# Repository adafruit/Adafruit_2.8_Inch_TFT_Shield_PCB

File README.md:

# 2.8" TFT Touch Shield for Arduino 

We've discontinued this version of the shield (which was expensive and difficult to make) and [replaced it with a version 2: its got a better price, uses way fewer pins, is Mega/Leonardo compatible and has a great touchscreen controller built in. Wow! Check it out here.](http://www.adafruit.com/products/1651)

Spice up your Arduino project with a beautiful large touchscreen display shield with built in microSD card connection. This TFT display is big (2.8" diagonal) bright (4 white-LED backlight) and colorful (18-bit 262,000 different shades)! 240x320 pixels with individual pixel control. It has way more resolution than a black and white 128x64 display. As a bonus, this display has a resistive touchscreen attached to it already, so you can detect finger presses anywhere on the screen.

__The shield is fully assembled, tested and ready to go. No wiring, no soldering! Simply plug it in and load up our library - you'll have it running in under 10 minutes!__ Works best with any classic Arduino (UNO/Duemilanove/Diecimila). This shield does work with the Mega Arduinos __but its going to be half the speed of the Uno-type boards__ because of the way the Mega rearranges all the pins (there is no way to get around this!) This shield is not Leonardo-compatible

This display shield has a controller built into it with RAM buffering, so that almost no work is done by the microcontroller. The shield does require a lot of pins: 12 lines total for the display, 13 total if you use the microSD card

[Of course, we wouldn't just leave you with a datasheet and a "good luck!" - we've written a full open source graphics library that can draw pixels, lines, rectangles, circles and text. We also have a touch screen library that detects x, y and z (pressure) and example code to demonstrate all of it. The code is written for Arduino but can be easily ported to your favorite microcontroller!](http://learn.adafruit.com/2-8-tft-touch-shield).

If you are not using an Arduino-shaped microcontroller, [check out our 2.8" TFT breakout board which can be easily wired up to any processor](http://www.adafruit.com/products/335) the breakout board version does not have microSD holder.

### TECHNICAL DETAILS

- 2.8" diagonal LCD TFT display
- 240x320 resolution, 18-bit (262,000) color
- ILI9325 (datasheet) or ILI9328 (datasheet) or HX8347 (datasheet) controller with built in video RAM buffer
- 8 bit digital interface, plus 4 control lines
- Uses digital pins 5-13 and analog 0-3. That means you can use digital pins 2, 3 and analog 4 and 5. Pin 12 is available if not using the microSD
- Works with any Arduino '328 or Mega (Leonardo not supported yet)
- 5V compatible! Use with 3.3V or 5V logic
- Onboard 3.3V @ 300mA LDO regulator
- 4 white LED backlight. On by default but you can connect the transistor to a digital pin for backlight control
- 4-wire resistive touchscreen

### License

Adafruit invests time and resources providing this open source design, please support Adafruit and open-source hardware by purchasing products from [Adafruit](https://www.adafruit.com)!

Designed by Limor Fried/Ladyada for Adafruit Industries.

Creative Commons Attribution/Share-Alike, all text above must be included in any redistribution. See license.txt for additional details.

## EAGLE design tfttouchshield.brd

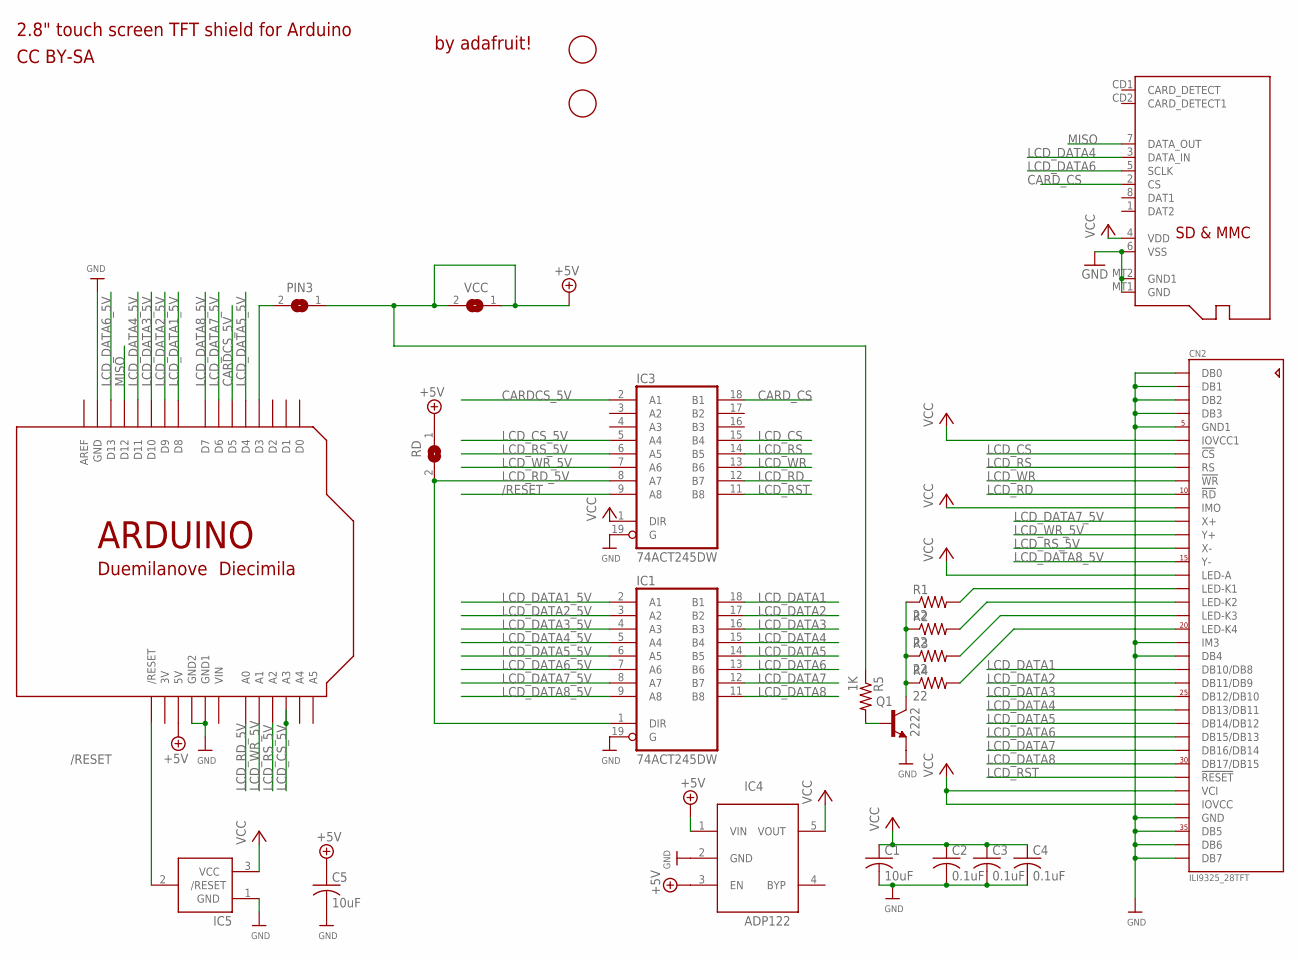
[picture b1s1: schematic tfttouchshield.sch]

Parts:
C1, C5: 10uF; C0805K
C2, C3, C4: 0.1uF; C0805K
CN2: ILI9325_28TFT; ILI9325_28INCH_TS
IC1, IC3: 74ACT245DW; SO20W
IC4: ADP122; SOT23-5L
IC5: AXP083-SAG; SOT23
PIN3: SJ
Q1: 2222; SOT23-BEC
R1, R2, R3, R4: 22; R0805
R5: 1K; R0805
RD: SJ
U$2: ARDUINO-NOHOLE
U$3: MICROSD
U$10, U$11: FIDUCIAL; FIDUCIAL_1MM
VCC: SJ

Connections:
3V: U$2.3V
+5V: C5.1, IC4.1 (VIN), IC4.3 (EN), PIN3.1, R5.1, RD.1, U$2.5V, VCC.1, VCC.2
/RESET: IC3.9 (A8), IC5.2 (/RESET), U$2.RESET (/RESET)
CARDCS_5V: IC3.2 (A1), U$2.D5
CARD_CS: IC3.18 (B1), U$3.2 (CS)
GND: C1.2, C2.2, C3.2, C4.2, C5.2, CN2.1 (DB0), CN2.2 (DB1), CN2.3 (DB2), CN2.4 (DB3), CN2.5 (GND1), CN2.21 (IM3), CN2.22 (DB4), CN2.34 (GND), CN2.35 (DB5), CN2.36 (DB6), CN2.37 (DB7), IC1.10 (GND), IC1.19 (G), IC3.10 (GND), IC3.19 (G), IC4.2 (GND), IC5.1 (GND), Q1.E, U$2.GND, U$2.GND1, U$2.GND2, U$3.6 (VSS), U$3.MT1 (GND), U$3.MT2 (GND1)
LCD_CS: CN2.7 (!CS), IC3.15 (B4)
LCD_CS_5V: IC3.5 (A4), U$2.A3
LCD_DATA1: CN2.23 (DB10/DB8), IC1.18 (B1)
LCD_DATA1_5V: IC1.2 (A1), U$2.D8
LCD_DATA2: CN2.24 (DB11/DB9), IC1.17 (B2)
LCD_DATA2_5V: IC1.3 (A2), U$2.D9
LCD_DATA3: CN2.25 (DB12/DB10), IC1.16 (B3)
LCD_DATA3_5V: IC1.4 (A3), U$2.D10
LCD_DATA4: CN2.26 (DB13/DB11), IC1.15 (B4), U$3.3 (DATA_IN)
LCD_DATA4_5V: IC1.5 (A4), U$2.D11
LCD_DATA5: CN2.27 (DB14/DB12), IC1.14 (B5)
LCD_DATA5_5V: IC1.6 (A5), U$2.D4
LCD_DATA6: CN2.28 (DB15/DB13), IC1.13 (B6), U$3.5 (SCLK)
LCD_DATA6_5V: IC1.7 (A6), U$2.D13
LCD_DATA7: CN2.29 (DB16/DB14), IC1.12 (B7)
LCD_DATA7_5V: CN2.12 (X+), IC1.8 (A7), U$2.D6
LCD_DATA8: CN2.30 (DB17/DB15), IC1.11 (B8)
LCD_DATA8_5V: CN2.15 (Y-), IC1.9 (A8), U$2.D7
LCD_RD: CN2.10 (!RD), IC3.12 (B7)
LCD_RD_5V: IC1.1 (DIR), IC3.8 (A7), RD.2, U$2.A0
LCD_RS: CN2.8 (RS), IC3.14 (B5)
LCD_RST: CN2.31 (!RESET), IC3.11 (B8)
LCD_RS_5V: CN2.14 (X-), IC3.6 (A5), U$2.A2
LCD_WR: CN2.9 (!WR), IC3.13 (B6)
LCD_WR_5V: CN2.13 (Y+), IC3.7 (A6), U$2.A1
MISO: U$2.D12, U$3.7 (DATA_OUT)
unnamed: CN2.20 (LED-K4), R4.2
unnamed: CN2.17 (LED-K1), R1.2
unnamed: CN2.18 (LED-K2), R2.2
unnamed: CN2.19 (LED-K3), R3.2
unnamed: Q1.C, R1.1, R2.1, R3.1, R4.1
unnamed: PIN3.2, U$2.D3
unnamed: Q1.B, R5.2
VCC: C1.1, C2.1, C3.1, C4.1, CN2.6 (IOVCC1), CN2.11 (IMO), CN2.16 (LED-A), CN2.32 (VCI), CN2.33 (IOVCC), IC1.20 (VCC), IC3.1 (DIR), IC3.20 (VCC), IC4.5 (VOUT), IC5.3 (VCC), U$3.4 (VDD)
VIN: U$2.VIN

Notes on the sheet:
2.8" touch screen TFT shield for Arduino
by adafruit!
CC BY-SA

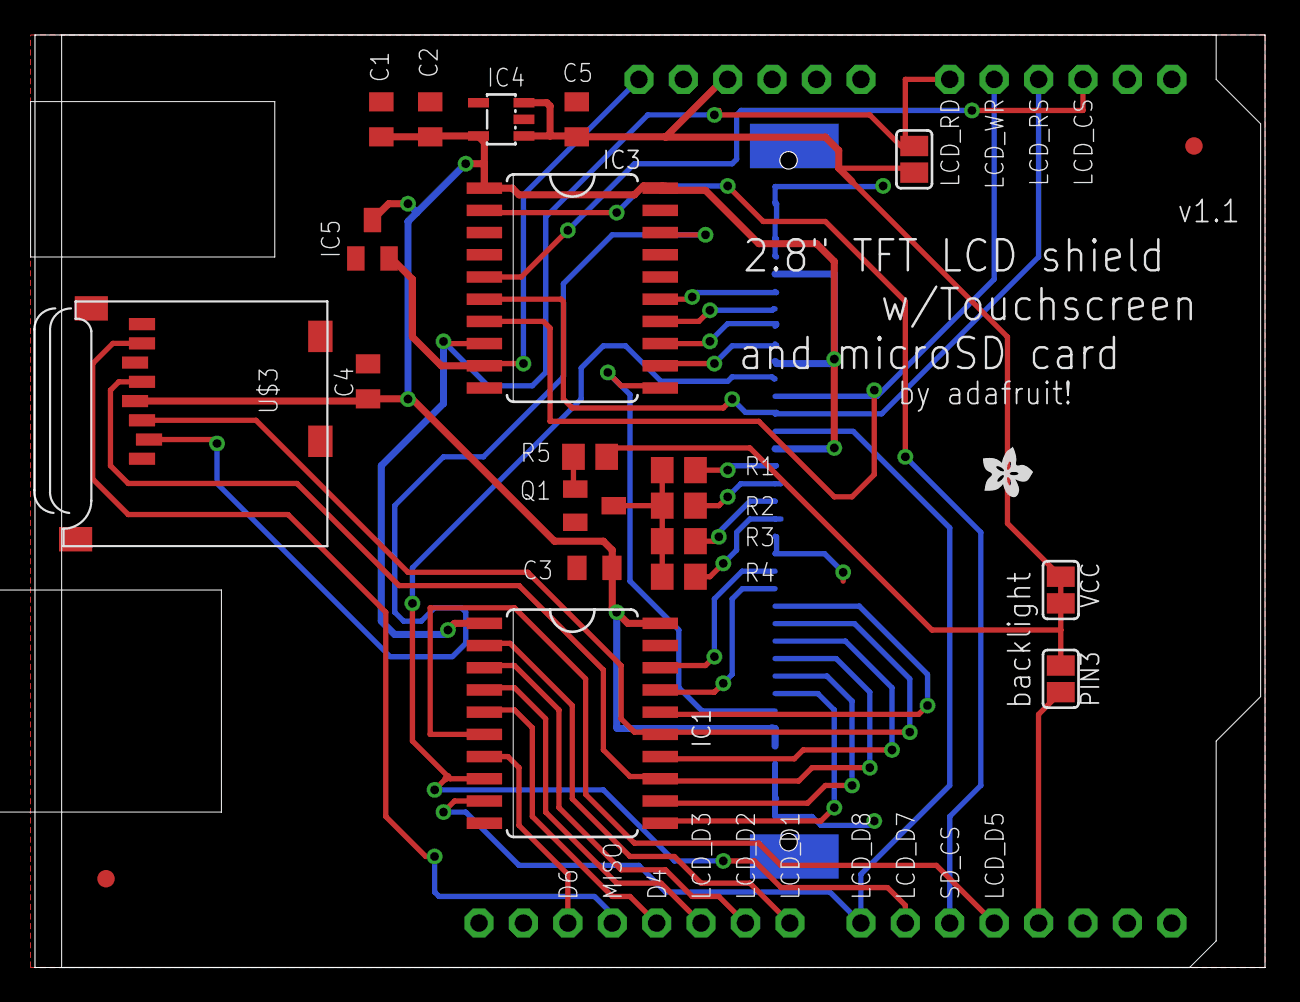
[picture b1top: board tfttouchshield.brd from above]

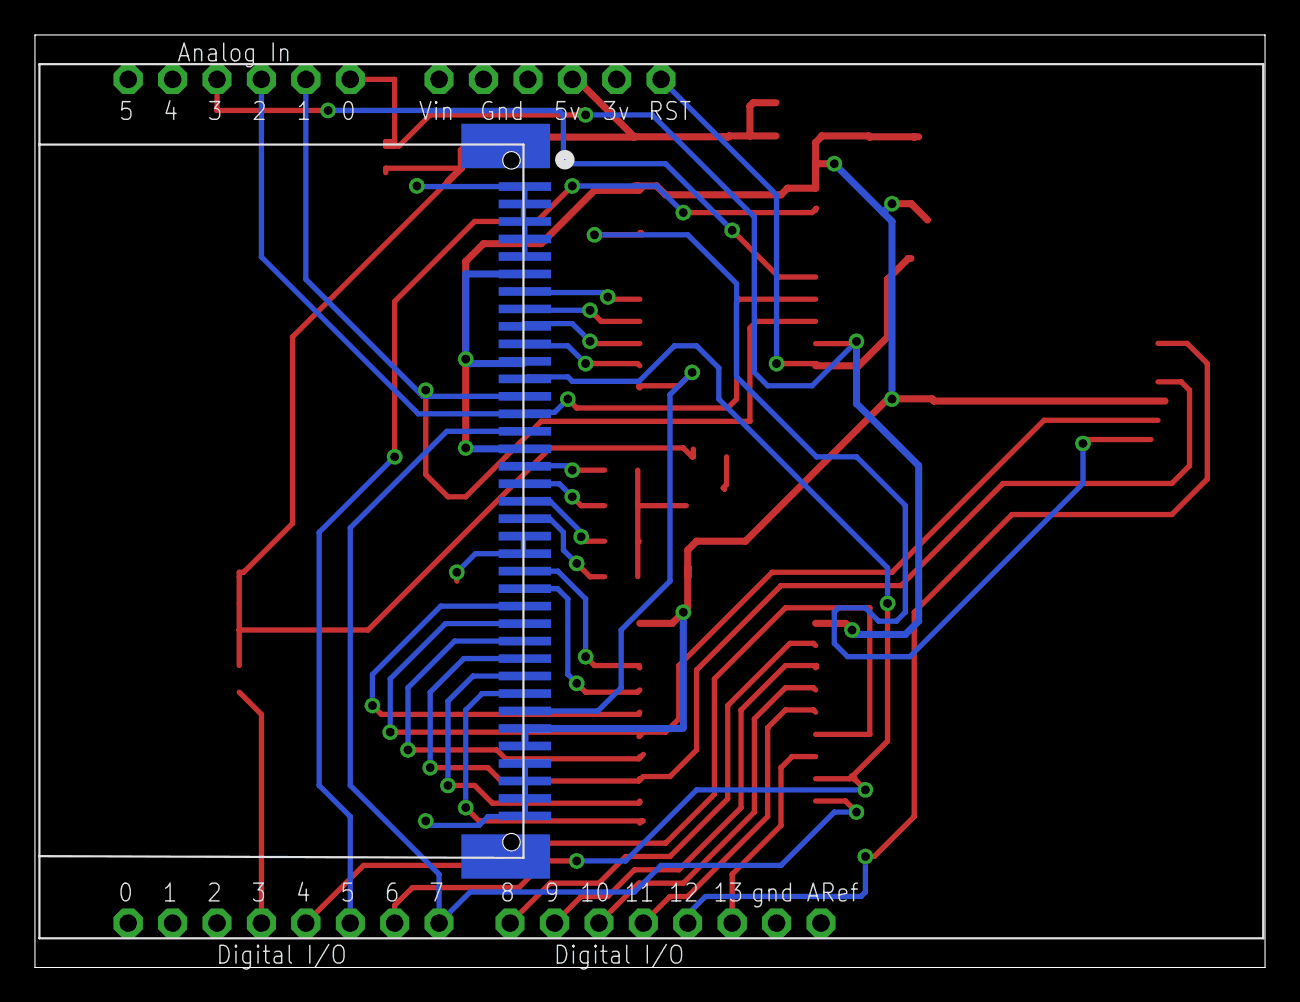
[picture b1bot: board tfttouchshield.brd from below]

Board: 2 copper layers, 70.4 x 53.3 mm, 25 parts (2 on the bottom side), 39 nets.

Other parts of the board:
U$7: ADAFRUIT200MIL
U$9: OSHWLOGO_TOL_0.2

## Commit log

2011-06-08 schem print
2011-10-18 Updated to latest minor rev, with better routing, and a jumper on RD
2019-03-21 readme + image
2019-07-17 adding license.txt
2019-07-17 added license to readme
2026-06-03 update file format to XML
